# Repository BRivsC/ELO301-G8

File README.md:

# ELO301 - Grupo 8
Este repositorio contiene los archivos para el ramo de  Diseño de Equipos Electrónicos.

Revisión más nueva de la PCB: Rev4
## Diseño
El documento de diseño y sus revisiones se encuentran en la carpeta de ```Diseño```.

## Esquemático
En la carpeta ```WIFI_Shield_Rev1``` se encuentra la primera revisión del esquemático junto a su Bill Of Materials en formato ```.csv```. 
El esquemático en sí está en la ruta ```WIFI_Shield_Rev1/WIFI_Shield_Rev1/SCHEMATIC_R1.sch```.

## Librerías
Las iteraciones anteriores de las librerías hechas por el grupo se encuentran en la carpeta ```Librerías``` . Las finalmente usadas se encuentran en su respectiva carpeta de proyecto.

## Diseño de la PCB

Contenido dentro de ```/WIFI_Shield_Rev2/WIFI_Shield_Rev2/SCHEMATIC_R1.brd```. Los archivos de manufactura se encuentran en ```/WIFI_Shield_Rev2/WIFI_SHIELD_2023-10-30.zip```

## Historial de revisiones del hardware

Rev 1: Revisión inicial.

Rev 2: Se ajustaron un par de pines para facilitar el ruteo y se ajustó la librería de la NUCLEO para eliminar los pines sin usar. 

Rev 3: Sustituídas las resistencias de 0 Ohm (R11, R12, R13 y R14) que separaban la UART y las resistencias para el EN (R16 y R17) hacia MCU o programador por 3 sets de jumpers 3x1.

Rev 4: Cambiados varios pines para usar la UART1 y el I2C3 de la STM en lugar de la UART2 y el I2C1 que provocaban conflictos

Agregadas instrucciones para usar los jumpers al otro lado de la placa.

## Firmware
Versión actual: Rev1

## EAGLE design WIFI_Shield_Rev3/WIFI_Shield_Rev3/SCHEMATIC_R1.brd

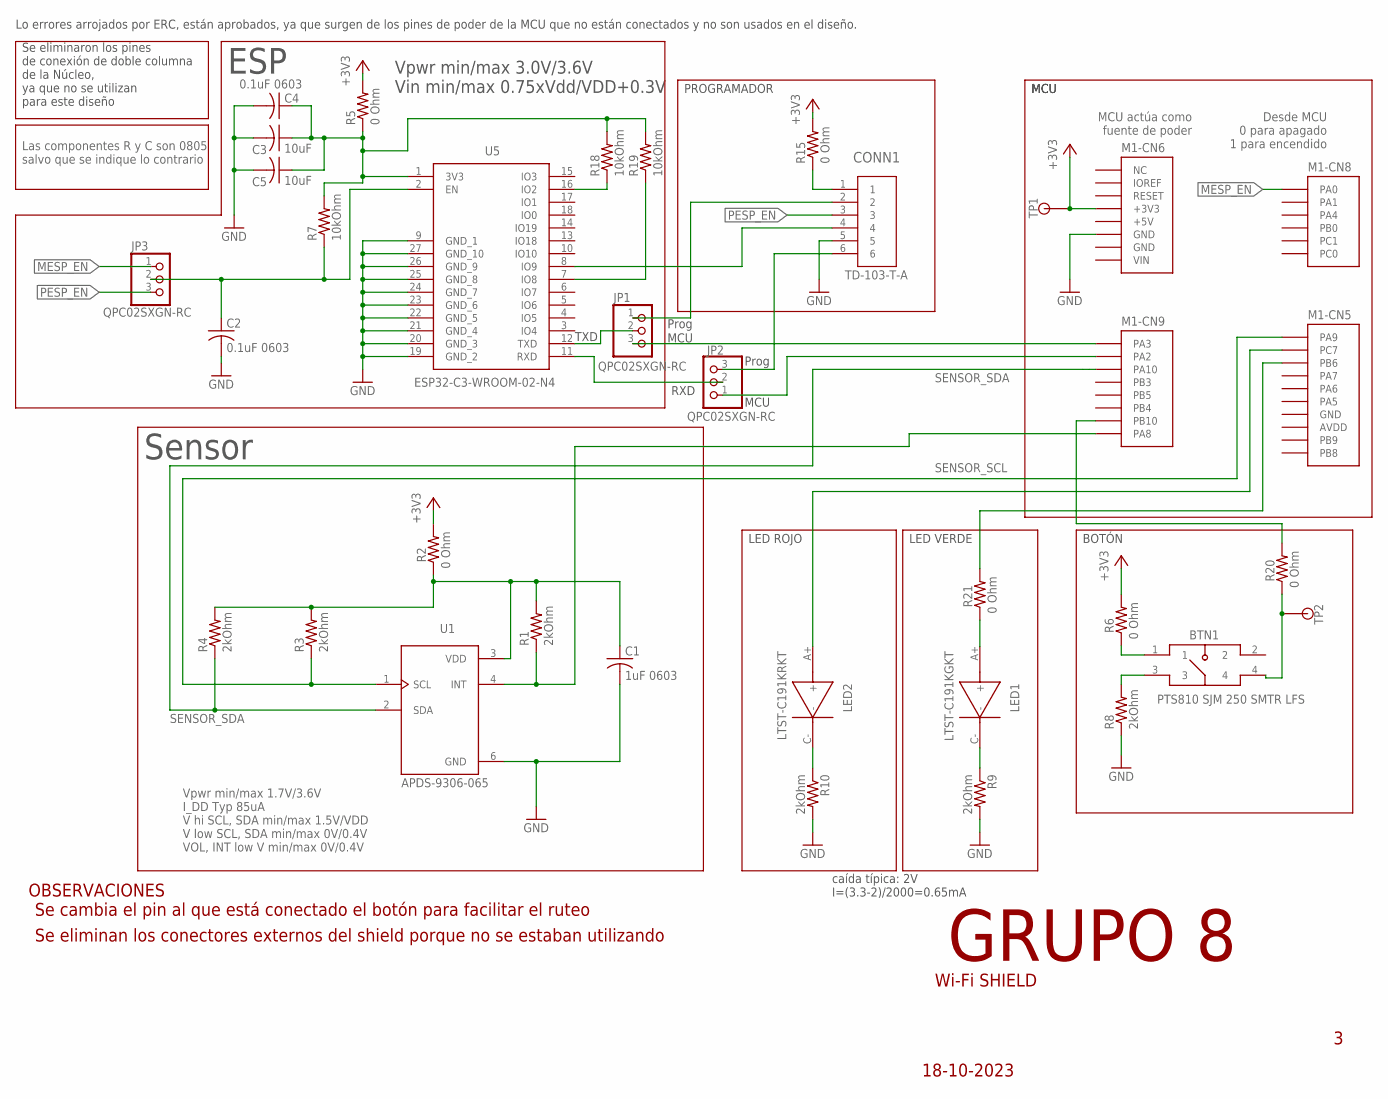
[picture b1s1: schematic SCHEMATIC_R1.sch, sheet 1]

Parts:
BTN1: PTS810 SJM 250 SMTR LFS; PTS810; PARTNO PTS810 SJM 250 SMTR LFS
C1: 1uF 0603; C0603; PARTNO GCM188R71C105KA64D
C2, C4: 0.1uF 0603; C0603; PARTNO GRM188R72A104KA35D
C3, C5: 10uF; C0805; PARTNO GRM21BR71A106KA73L
CONN1: TD-103-T-A; CON6_2X3_TU_HTS_SAI; PARTNO TD-103-T-A
JP1, JP2, JP3: QPC02SXGN-RC; 1X03; PARTNO QPC02SXGN-RC
LED1: LTST-C191KGKT; 0603; PARTNO LTST-C191KGKT
LED2: LTST-C191KRKT; 0603; PARTNO LTST-C191KRKT
M1: NUCLEO-L452RE; NUCLEO-64; PARTNO NUCLEO-L452RE
R1, R3, R4, R8, R9, R10: 2kOhm; M0805; PARTNO RMCF0805FT2K00
R2, R5, R6, R15, R20, R21: 0 Ohm; M0805; PARTNO RMCF0805ZT0R00
R7, R18, R19: 10kOhm; R0805; PARTNO RMCF0805JT10K0
TP1, TP2: TESTPOINT
U1: APDS-9306-065; SON65P200X200X75-6N; PARTNO APDS-9306-065
U5: ESP32-C3-WROOM-02-N4; ESP32C3WROOM02N4; PARTNO ESP32-C3-WROOM-02-N4

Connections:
+3V3: M1.CN6-4 (+3V3), R2.2, R5.2, R6.2, R15.2, TP1.TP
+5V: M1.CN6-5 (+5V)
AVDD: M1.CN5-8 (AVDD)
GND: C1.2, C2.2, C3.2, C4.2, C5.2, CONN1.5, M1.CN5-7 (GND), M1.CN6-6 (GND), M1.CN6-7 (GND), R8.1, R9.2, R10.2, U1.6 (GND), U5.9 (GND_1), U5.19 (GND_2), U5.20 (GND_3), U5.21 (GND_4), U5.22 (GND_5), U5.23 (GND_6), U5.24 (GND_7), U5.25 (GND_8), U5.26 (GND_9), U5.27 (GND_10)
IOREF: M1.CN6-2 (IOREF)
MESP_EN: JP3.1, M1.CN8-1 (PA0)
unnamed: M1.CN9-7 (PB10), R20.2
unnamed: C1.1, R1.2, R2.1, R3.2, R4.2, U1.3 (VDD)
unnamed: M1.CN9-8 (PA8), R1.1, U1.4 (INT)
unnamed: LED2.A+ (+), M1.CN5-2 (PC7)
unnamed: BTN1.3, R8.2
unnamed: R18.1, U5.16 (IO2)
unnamed: BTN1.1, R6.1
unnamed: JP1.3, M1.CN9-1 (PA3)
unnamed: JP2.1, M1.CN9-2 (PA2)
unnamed: BTN1.4, R20.1, TP2.TP
unnamed: M1.CN5-3 (PB6), R21.2
unnamed: LED2.C- (-), R10.1
unnamed: LED1.C- (-), R9.1
unnamed: JP2.2, U5.11 (RXD)
unnamed: CONN1.2, JP1.1
unnamed: CONN1.6, JP2.3
unnamed: CONN1.4, U5.8 (IO9)
unnamed: CONN1.1, R15.1
unnamed: R19.1, U5.7 (IO8)
unnamed: C2.1, JP3.2, R7.1, U5.2 (EN)
unnamed: C3.1, C4.1, C5.1, R5.1, R7.2, R18.2, R19.2, U5.1 (3V3)
unnamed: LED1.A+ (+), R21.1
unnamed: JP1.2, U5.12 (TXD)
PESP_EN: CONN1.3, JP3.3
SENSOR_SCL: M1.CN5-1 (PA9), R3.1, U1.1 (SCL)
SENSOR_SDA: M1.CN9-3 (PA10), R4.1, U1.2 (SDA)
VIN: M1.CN6-8 (VIN)

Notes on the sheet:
Vpwr min/max 3.0V/3.6V Vin min/max 0.75xVdd/VDD+0.3V
Vpwr min/max 1.7V/3.6V I_DD Typ 85uA V hi SCL, SDA min/max 1.5V/VDD V low SCL, SDA min/max 0V/0.4V VOL, INT low V min/max 0V/0.4V
Las componentes R y C son 0805 salvo que se indique lo contrario
Desde MCU 0 para apagado 1 para encendido
caída típica: 2V I=(3.3-2)/2000=0.65mA
Se eliminaron los pines de conexión de doble columna de la Núcleo, ya que no se utilizan para este diseño
Sensor
LED ROJO
LED VERDE
BOTÓN
MCU
PROGRAMADOR
ESP
MCU actúa como fuente de poder
Lo errores arrojados por ERC, están aprobados, ya que surgen de los pines de poder de la MCU que no están conectados y no son usados en el diseño.
Wi-Fi SHIELD
18-10-2023
GRUPO 8
Se cambia el pin al que está conectado el botón para facilitar el ruteo
OBSERVACIONES
Se eliminan los conectores externos del shield porque no se estaban utilizando
RXD
Prog
TXD

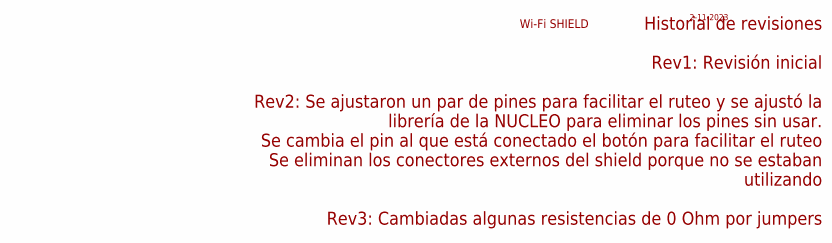
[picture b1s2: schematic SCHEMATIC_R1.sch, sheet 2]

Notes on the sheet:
Wi-Fi SHIELD
2-11-2023
Historial de revisiones Rev1: Revisión inicial Rev2: Se ajustaron un par de pines para facilitar el ruteo y se ajustó la librería de la NUCLEO para eliminar los pines sin usar. Se cambia el pin al que está conectado el botón para facilitar el ruteo Se eliminan los conectores externos del shield por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

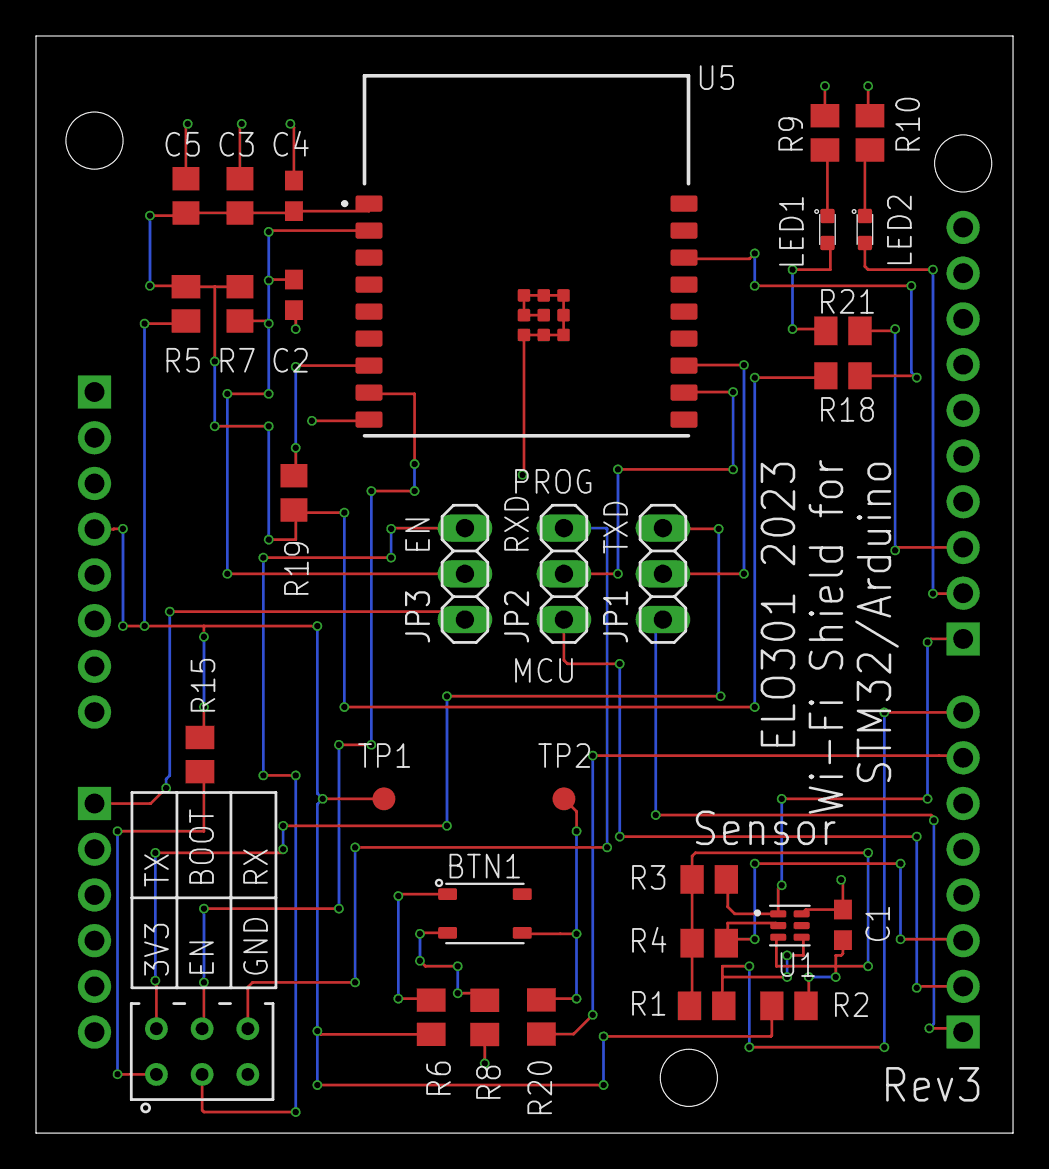
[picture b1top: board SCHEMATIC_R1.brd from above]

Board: 2 copper layers, 54.3 x 60.9 mm, 32 parts (0 on the bottom side), 29 nets.

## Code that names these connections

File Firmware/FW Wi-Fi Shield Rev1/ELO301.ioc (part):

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Mcu.Name=STM32L452R(C-E)Tx
Mcu.Package=LQFP64
Mcu.UserName=STM32L452RETx
PA0.GPIOParameters=GPIO_Label
PA0.GPIO_Label=MESP_EN
PA0.Signal=GPIO_Output
PA10.GPIOParameters=GPIO_Label
PA10.GPIO_Label=RX_STM
PA10.Mode=Asynchronous
PA10.Signal=USART1_RX
PA13\ (JTMS/SWDIO).GPIOParameters=GPIO_Label
PA13\ (JTMS/SWDIO).GPIO_Label=TMS
PA13\ (JTMS/SWDIO).Mode=Serial_Wire
PA13\ (JTMS/SWDIO).Signal=SYS_JTMS-SWDIO
PA14\ (JTCK/SWCLK).GPIOParameters=GPIO_Label
PA14\ (JTCK/SWCLK).GPIO_Label=TCK
PA14\ (JTCK/SWCLK).Mode=Serial_Wire
PA14\ (JTCK/SWCLK).Signal=SYS_JTCK-SWCLK
PA2.GPIOParameters=GPIO_Speed,GPIO_PuPd,GPIO_Label,GPIO_Mode
PA2.GPIO_Label=USART_TX
PA2.GPIO_Mode=GPIO_MODE_AF_PP
PA2.GPIO_PuPd=GPIO_NOPULL
PA2.GPIO_Speed=GPIO_SPEED_FREQ_VERY_HIGH
PA2.Mode=Asynchronous
PA2.Signal=USART2_TX
PA3.GPIOParameters=GPIO_Speed,GPIO_PuPd,GPIO_Label,GPIO_Mode
PA3.GPIO_Label=USART_RX
PA3.GPIO_Mode=GPIO_MODE_AF_PP
PA3.GPIO_PuPd=GPIO_NOPULL
PA3.GPIO_Speed=GPIO_SPEED_FREQ_VERY_HIGH
PA3.Mode=Asynchronous
PA3.Signal=USART2_RX
PA5.GPIOParameters=GPIO_Speed,GPIO_PuPd,GPIO_Label,GPIO_ModeDefaultOutputPP
PA5.GPIO_Label=LD4 [green Led]
PA5.GPIO_ModeDefaultOutputPP=GPIO_MODE_OUTPUT_PP
PA5.GPIO_PuPd=GPIO_NOPULL
PA5.GPIO_Speed=GPIO_SPEED_FREQ_LOW
PA5.Signal=GPIO_Output
PA8.GPIOParameters=GPIO_Label
PA8.GPIO_Label=SENSOR_INT
PA8.Signal=GPXTI8
PA9.GPIOParameters=GPIO_Label
PA9.GPIO_Label=TX_STM
PA9.Mode=Asynchronous
PA9.Signal=USART1_TX
PB10.GPIOParameters=GPIO_Label
PB10.GPIO_Label=GPIO_BOTON
PB10.Signal=GPXTI10
PB3\ (JTDO/TRACESWO).GPIOParameters=GPIO_Label
PB3\ (JTDO/TRACESWO).GPIO_Label=SWO
PB3\ (JTDO/TRACESWO).Signal=SYS_JTDO-SWO
PB6.GPIOParameters=GPIO_Label
PB6.GPIO_Label=GPIO_LED_ROJO
PB6.Signal=GPIO_Output
PC0.GPIOParameters=GPIO_Label
PC0.GPIO_Label=SENSOR_SCL
PC0.Signal=I2C3_SCL
PC1.GPIOParameters=GPIO_Label
PC1.GPIO_Label=SENSOR_SDA
PC1.Signal=I2C3_SDA
PC13.GPIOParameters=GPIO_PuPd,GPIO_Label,GPIO_ModeDefaultEXTI
PC13.GPIO_Label=B1 [Blue PushButton]
PC13.GPIO_ModeDefaultEXTI=GPIO_MODE_IT_FALLING
PC13.GPIO_PuPd=GPIO_NOPULL
PC13.Signal=GPXTI13
PC14-OSC32_IN\ (PC14).Mode=LSE-External-Oscillator
PC14-OSC32_IN\ (PC14).Signal=RCC_OSC32_IN
PC15-OSC32_OUT\ (PC15).Mode=LSE-External-Oscillator
PC15-OSC32_OUT\ (PC15).Signal=RCC_OSC32_OUT
PC7.GPIOParameters=GPIO_Label
PC7.GPIO_Label=GPIO_LED_VERDE
PC7.Signal=GPIO_Output
PH0-OSC_IN\ (PH0).Signal=RCC_OSC_IN
PH1-OSC_OUT\ (PH1).Signal=RCC_OSC_OUT
RCC.HSE_VALUE=8000000
RCC.SYSCLKFreq_VALUE=80000000
RCC.SYSCLKSource=RCC_SYSCLKSOURCE_PLLCLK
board=NUCLEO-L452RE
boardIOC=true

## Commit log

2023-10-19 Eliminadas versiones previas del esquemático
2023-10-19 Agregada la segunda revisión del doc de diseño
2023-10-19 Agregada la ruta al .sch del esquemático
2023-10-23 Se modifica disposicion de componentes en la placa
2023-10-29 Se sube revison 2. En esta revisoón se cambia el pin del booón y se modifica un poco la libreria del shield nucleo
2023-10-29 Se agrega archivo gitignore a Rev2
2023-10-30 Corregidos algunos wire stubs. Cambiado IO9 por BOOT en Silkscreen
2023-10-30 Añadida información al README y versiones antiguas
2023-10-30 Agregado el BOM correspondiente
2023-10-30 Agregados BOM y archivos de manufactura
2023-10-30 Eliminado el BOM fallido
2023-11-02 Agregada Rev3. Leer README para más información
2023-11-03 Arreglados los jumpers que no aparecían en el BOM. Agregados comentarios adicionales
2023-11-10 Agregada la base del firmware
2023-11-10 Revisión 4: Cambiado el UART y el I2C
2023-11-13 Actualizado el .ioc para remapear los pines a lo del HW Rev4
2023-11-17 Se agrega FW con ma´quina de estados implementada. Falta agregar estados para que funcionen comandos at
2023-11-28 Arreglada la máquina de estados y agregado el test del sensor
2023-12-01 Correcciones menores en el test del sensor
2023-12-01 Actualizado para enviar el valor del clock a ThingSpeak
2023-12-03 Arreglos menores en el test del sensor
2023-12-05 Rev1: Primera versión completamente funcional.

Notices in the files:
parts and their libraries:
COPYRIGHT: Copyright (C) 2023 Ultra Librarian. All rights reserved.
